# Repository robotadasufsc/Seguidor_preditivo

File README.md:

# Seguidor_preditivo
Repositório do seguidor de linha com controle preditivo

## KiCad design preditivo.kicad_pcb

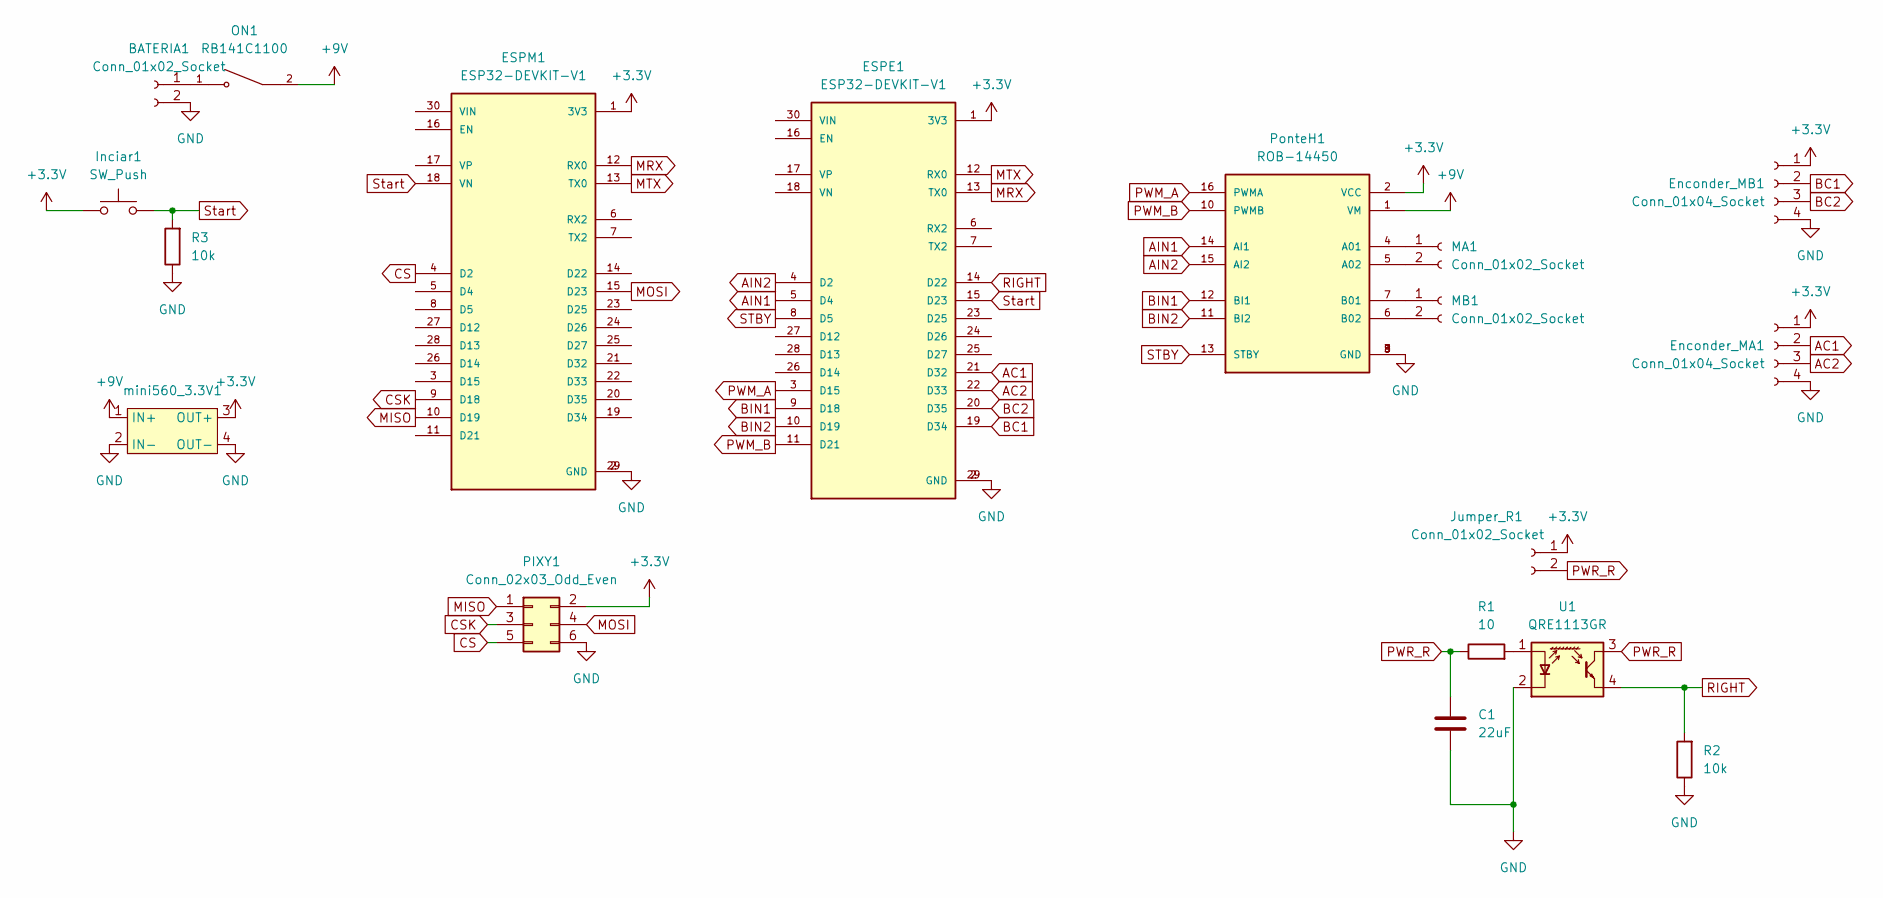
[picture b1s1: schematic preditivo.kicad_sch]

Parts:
BATERIA1: Conn_01x02_Socket; JST_EH_B2B-EH-A_1x02_P2.50mm_Vertical
C1: 22uF; CP_Radial_D8.0mm_P3.80mm
ESPE1: ESP32-DEVKIT-V1; ESP32_DEVKIT_V1; PARTREV N/A
ESPM1: ESP32-DEVKIT-V1; ESP32_DEVKIT_V1; PARTREV N/A
Enconder_MA1: Conn_01x04_Socket; JST_EH_B4B-EH-A_1x04_P2.50mm_Vertical
Enconder_MB1: Conn_01x04_Socket; JST_EH_B4B-EH-A_1x04_P2.50mm_Vertical
Inciar1: SW_Push; SW_PUSH_6mm
Jumper_R1: Conn_01x02_Socket; JST_EH_B2B-EH-A_1x02_P2.50mm_Vertical
MA1: Conn_01x02_Socket; JST_EH_B2B-EH-A_1x02_P2.50mm_Vertical
MB1: Conn_01x02_Socket; JST_EH_B2B-EH-A_1x02_P2.50mm_Vertical
ON1: RB141C1100; SW_RB141C1100; PARTREV C
PIXY1: Conn_02x03_Odd_Even; IDC-Header_2x03_P2.54mm_Vertical
PonteH1: ROB-14450; MODULE_ROB-14450; PARTREV 11-13-17
R1: 10; R_Axial_DIN0204_L3.6mm_D1.6mm_P7.62mm_Horizontal
R2, R3: 10k; R_Axial_DIN0204_L3.6mm_D1.6mm_P7.62mm_Horizontal
U1: QRE1113GR; OnSemi_CASE100CY
mini560_3.3V1: mini560_3.3V

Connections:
+3.3V: ESPE1.1 (3V3), ESPM1.1 (3V3), Enconder_MA1.1, Enconder_MB1.1, Inciar1.1, Jumper_R1.1, PIXY1.2, PonteH1.2 (VCC), mini560_3.3V1.3 (OUT+)
+9V: ON1.2, PonteH1.1 (VM), mini560_3.3V1.1 (IN+)
AC1: ESPE1.21 (D32), Enconder_MA1.2
AC2: ESPE1.22 (D33), Enconder_MA1.3
AIN1: ESPE1.5 (D4), PonteH1.14 (AI1)
AIN2: ESPE1.4 (D2), PonteH1.15 (AI2)
BC1: ESPE1.19 (D34), Enconder_MB1.2
BC2: ESPE1.20 (D35), Enconder_MB1.3
BIN1: ESPE1.9 (D18), PonteH1.12 (BI1)
BIN2: ESPE1.10 (D19), PonteH1.11 (BI2)
CS: ESPM1.4 (D2), PIXY1.5
CSK: ESPM1.9 (D18), PIXY1.3
GND: BATERIA1.2, C1.2, ESPE1.2 (GND), ESPE1.29 (GND), ESPM1.2 (GND), ESPM1.29 (GND), Enconder_MA1.4, Enconder_MB1.4, PIXY1.6, PonteH1.3 (GND), PonteH1.8 (GND), PonteH1.9 (GND), R2.1, R3.1, U1.2 (K), mini560_3.3V1.2 (IN-), mini560_3.3V1.4 (OUT-)
MISO: ESPM1.10 (D19), PIXY1.1
MOSI: ESPM1.15 (D23), PIXY1.4
MRX: ESPE1.13 (TX0), ESPM1.12 (RX0)
MTX: ESPE1.12 (RX0), ESPM1.13 (TX0)
unnamed: BATERIA1.1, ON1.1
unnamed: MA1.1, PonteH1.4 (A01)
unnamed: MA1.2, PonteH1.5 (A02)
unnamed: MB1.1, PonteH1.7 (B01)
unnamed: MB1.2, PonteH1.6 (B02)
unnamed: R1.2, U1.1 (A)
PWM_A: ESPE1.3 (D15), PonteH1.16 (PWMA)
PWM_B: ESPE1.11 (D21), PonteH1.10 (PWMB)
PWR_R: C1.1, Jumper_R1.2, R1.1, U1.3
RIGHT: ESPE1.14 (D22), R2.2, U1.4
STBY: ESPE1.8 (D5), PonteH1.13 (STBY)
Start: ESPE1.15 (D23), ESPM1.18 (VN), Inciar1.2, R3.2

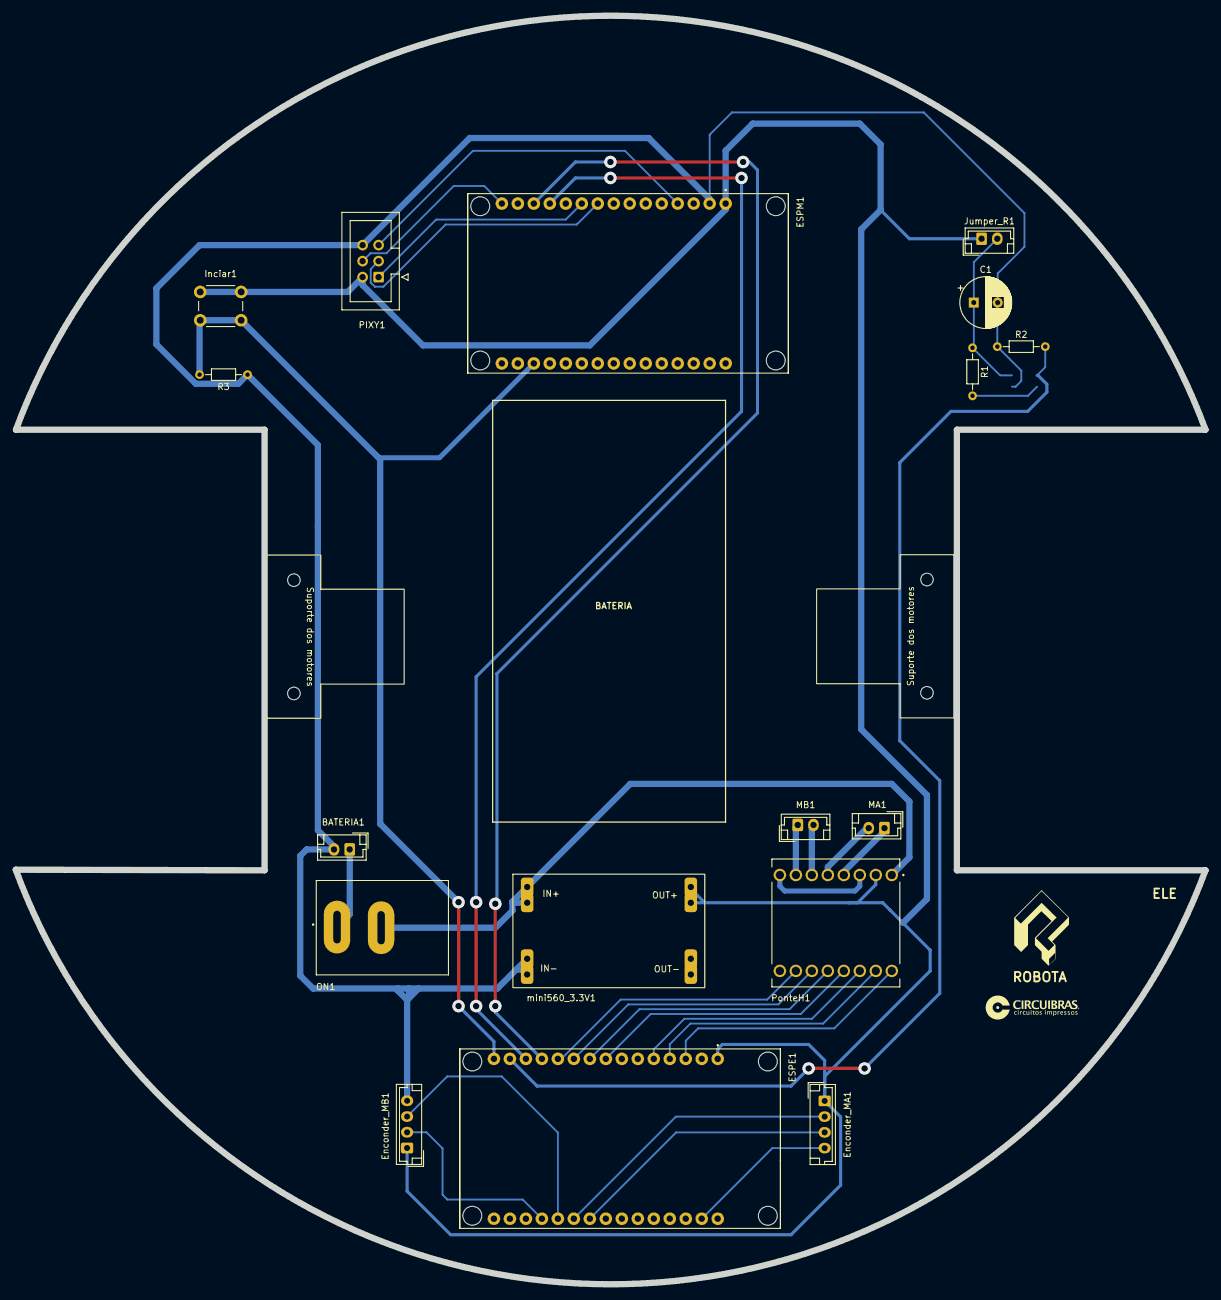
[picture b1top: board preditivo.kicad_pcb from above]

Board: 2 copper layers, 189.0 x 201.5 mm, 21 parts (1 on the bottom side), 29 nets.

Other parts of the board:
ROBOTA: LOGO; logo
Suporte dos motores: suporte
Suporte dos motores#2: suporte

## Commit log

2023-06-30 Add files via upload
    A placa desta versão utiliza apenas uma face
